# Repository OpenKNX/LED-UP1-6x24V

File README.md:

# LED-UP1-6x24V
OpenKNX 6channel LED PWM Controller up to 24V

see https://github.com/OpenKNX/OpenKNX/wiki/LED-UP1-6x24V

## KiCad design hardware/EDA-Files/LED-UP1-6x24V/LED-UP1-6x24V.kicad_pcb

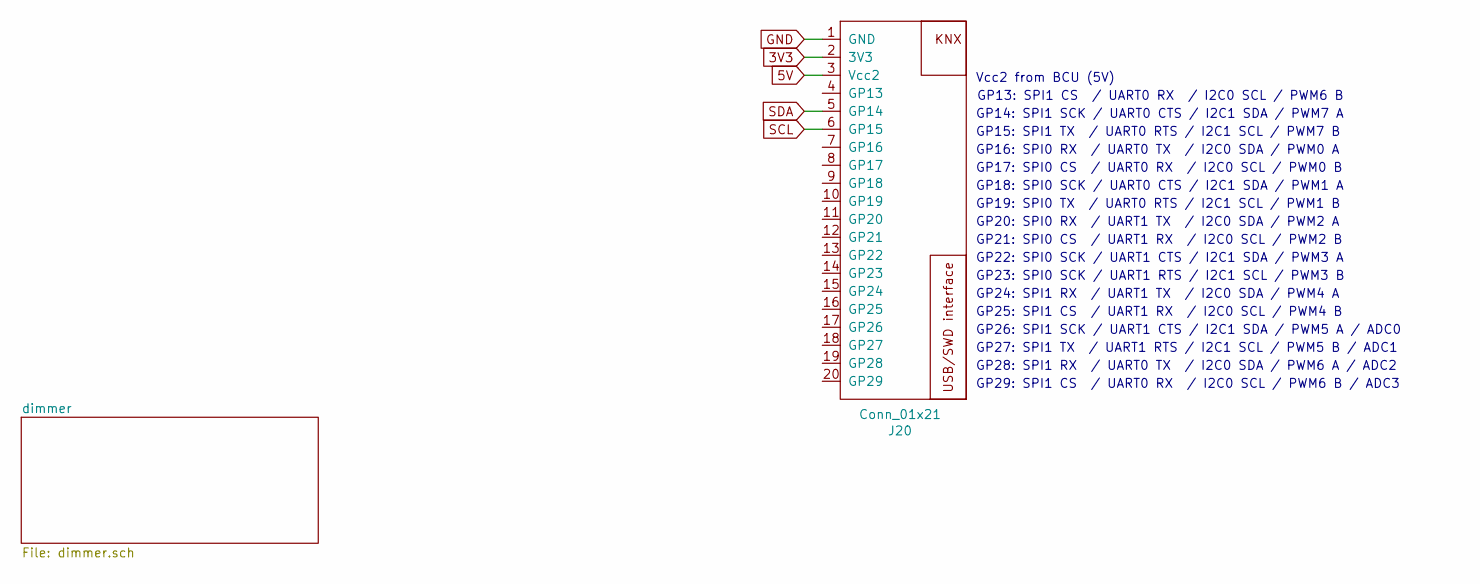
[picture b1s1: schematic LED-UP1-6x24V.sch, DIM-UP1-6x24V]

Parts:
J20: Conn_01x21; OpenKNX_UP1-PCBConnector_1x20_App_3D

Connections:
3V3: J20.2 (3V3); also elsewhere on the board
5V: J20.3 (Vcc2)
GND: J20.1 (GND); also elsewhere on the board
SCL: J20.6 (GP15); also elsewhere on the board
SDA: J20.5 (GP14); also elsewhere on the board

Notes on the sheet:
GP14: SPI1 SCK / UART0 CTS / I2C1 SDA / PWM7 A
GP15: SPI1 TX / UART0 RTS / I2C1 SCL / PWM7 B
GP18: SPI0 SCK / UART0 CTS / I2C1 SDA / PWM1 A
GP19: SPI0 TX / UART0 RTS / I2C1 SCL / PWM1 B
GP17: SPI0 CS / UART0 RX / I2C0 SCL / PWM0 B
GP16: SPI0 RX / UART0 TX / I2C0 SDA / PWM0 A
GP13: SPI1 CS / UART0 RX / I2C0 SCL / PWM6 B
GP20: SPI0 RX / UART1 TX / I2C0 SDA / PWM2 A
GP21: SPI0 CS / UART1 RX / I2C0 SCL / PWM2 B
GP22: SPI0 SCK / UART1 CTS / I2C1 SDA / PWM3 A
GP23: SPI0 SCK / UART1 RTS / I2C1 SCL / PWM3 B
GP24: SPI1 RX / UART1 TX / I2C0 SDA / PWM4 A
GP25: SPI1 CS / UART1 RX / I2C0 SCL / PWM4 B
GP26: SPI1 SCK / UART1 CTS / I2C1 SDA / PWM5 A / ADC0
GP27: SPI1 TX / UART1 RTS / I2C1 SCL / PWM5 B / ADC1
GP28: SPI1 RX / UART0 TX / I2C0 SDA / PWM6 A / ADC2
GP29: SPI1 CS / UART0 RX / I2C0 SCL / PWM6 B / ADC3
Vcc2 from BCU (5V)

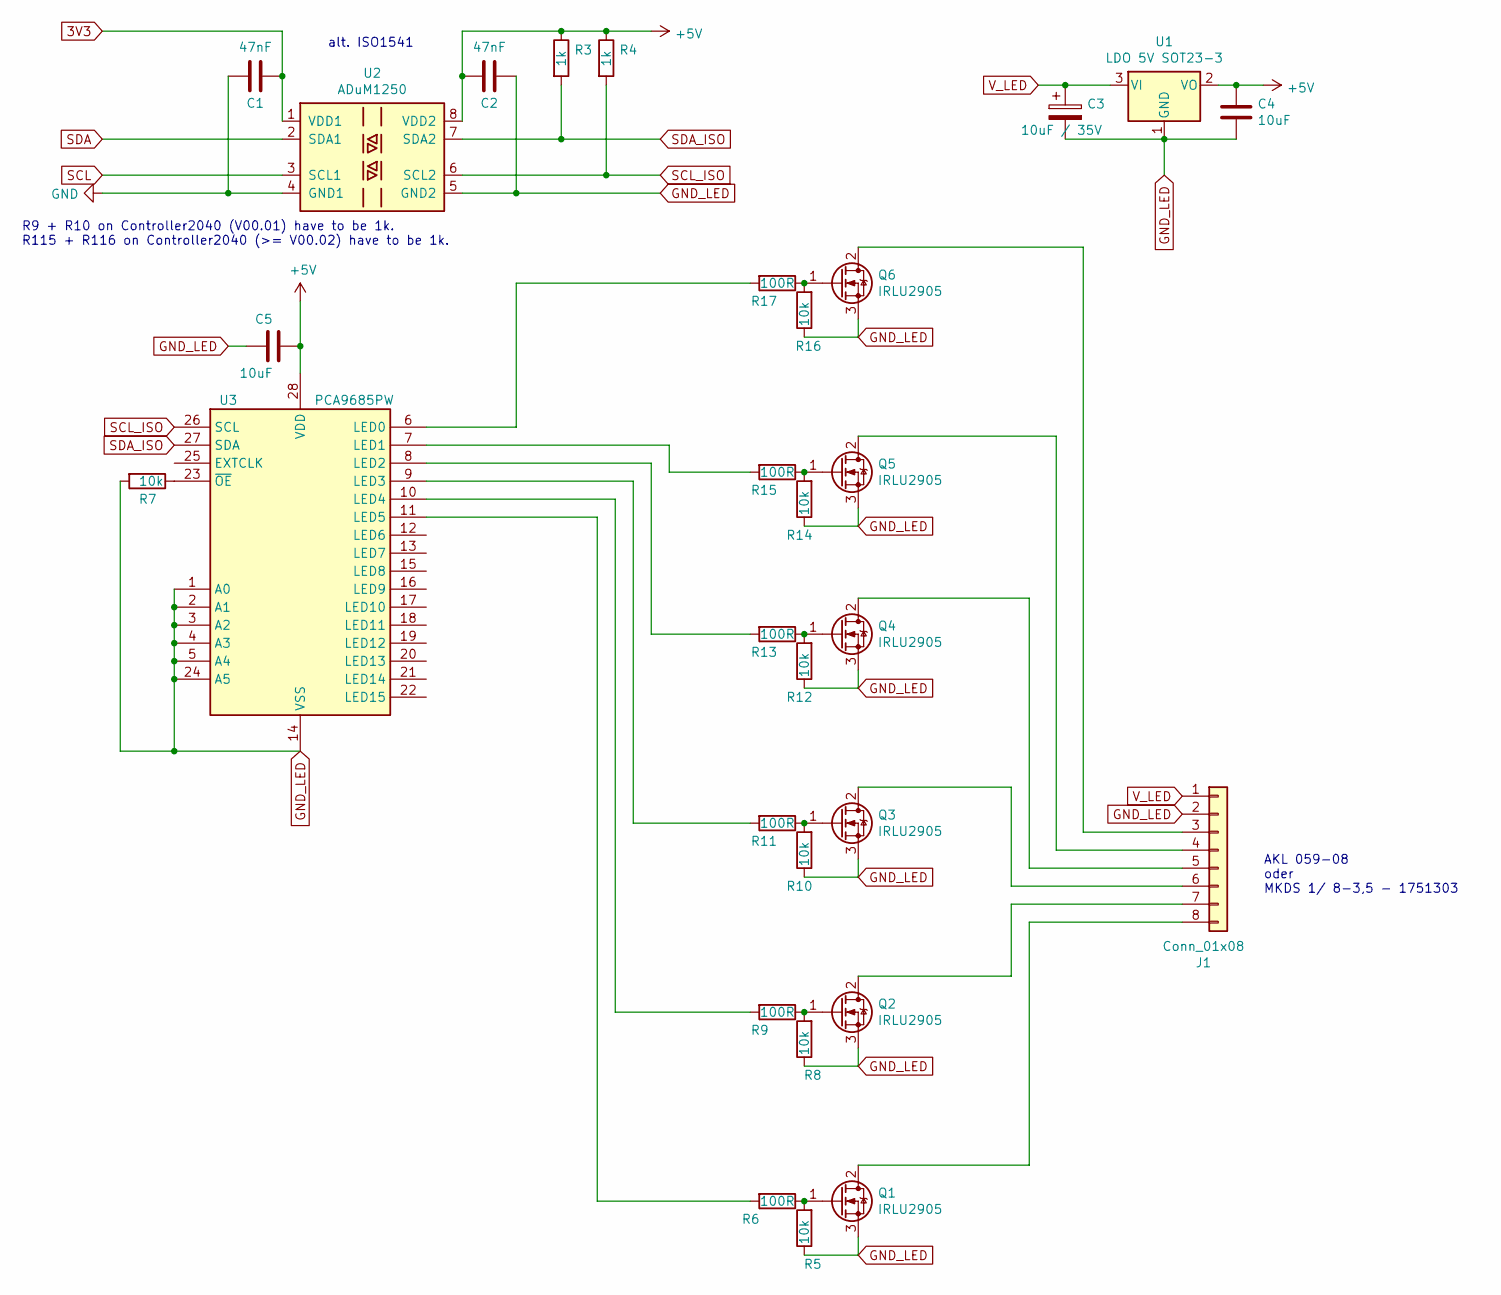
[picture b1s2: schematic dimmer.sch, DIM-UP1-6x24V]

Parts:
C1, C2: 47nF; C_0805_2012Metric_Pad1.15x1.40mm_HandSolder
C3: 10uF / 35V; CP_Elec_5x5.3
C4: 10uF; C_0603_1608Metric_Pad1.05x0.95mm_HandSolder
C5: 10uF; C_0805_2012Metric
J1: Conn_01x08; PhoenixContact_MKDS_1,5_8-G-3.5_1x08_P3.5mm_Horizontal
Q1, Q2, Q3, Q4, Q5, Q6: IRLU2905; TO-251-3_Vertical_lowprofile
R3, R4: 1k; R_0603_1608Metric_Pad1.05x0.95mm_HandSolder
R5, R7, R8, R10, R12, R14, R16: 10k; R_0603_1608Metric_Pad1.05x0.95mm_HandSolder
R6, R9, R11, R13, R15, R17: 100R; R_0603_1608Metric_Pad1.05x0.95mm_HandSolder
U1: LDO 5V SOT23-3; TSOT-23
U2: ADuM1250; SSOP-8_3.9x5.05mm_P1.27mm
U3: PCA9685PW; TSSOP-28_4.4x9.7mm_P0.65mm_Handsolder

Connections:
3V3: C1.1, U2.1 (VDD1); also elsewhere on the board
+5V: C2.2, C4.1, C5.2, R3.1, R4.1, U1.2 (VO), U2.8 (VDD2), U3.28 (VDD)
GND: C1.2, U2.4 (GND1); also elsewhere on the board
GND_LED: C2.1, C3.2, C4.2, C5.1, J1.2, Q1.3 (S), Q2.3 (S), Q3.3 (S), Q4.3 (S), Q5.3 (S), Q6.3 (S), R5.1, R7.2, R8.1, R10.1, R12.1, R14.1, R16.1, U1.1 (GND), U2.5 (GND2), U3.1 (A0), U3.2 (A1), U3.3 (A2), U3.4 (A3), U3.5 (A4), U3.14 (VSS), U3.24 (A5)
unnamed: J1.3, Q6.2 (D)
unnamed: J1.4, Q5.2 (D)
unnamed: J1.5, Q4.2 (D)
unnamed: J1.6, Q3.2 (D)
unnamed: J1.7, Q2.2 (D)
unnamed: J1.8, Q1.2 (D)
unnamed: Q1.1 (G), R5.2, R6.1
unnamed: Q2.1 (G), R8.2, R9.1
unnamed: Q3.1 (G), R10.2, R11.1
unnamed: Q4.1 (G), R12.2, R13.1
unnamed: Q5.1 (G), R14.2, R15.1
unnamed: Q6.1 (G), R16.2, R17.1
unnamed: R6.2, U3.11 (LED5)
unnamed: R7.1, U3.23 (~OE)
unnamed: R9.2, U3.10 (LED4)
unnamed: R11.2, U3.9 (LED3)
unnamed: R13.2, U3.8 (LED2)
unnamed: R15.2, U3.7 (LED1)
unnamed: R17.2, U3.6 (LED0)
SCL: U2.3 (SCL1); also elsewhere on the board
SCL_ISO: R4.2, U2.6 (SCL2), U3.26 (SCL)
SDA: U2.2 (SDA1); also elsewhere on the board
SDA_ISO: R3.2, U2.7 (SDA2), U3.27 (SDA)
V_LED: C3.1, J1.1, U1.3 (VI)

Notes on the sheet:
AKL 059-08 oder MKDS 1/ 8-3,5 - 1751303
R9 + R10 on Controller2040 (V00.01) have to be 1k. R115 + R116 on Controller2040 (>= V00.02) have to be 1k.
alt. ISO1541

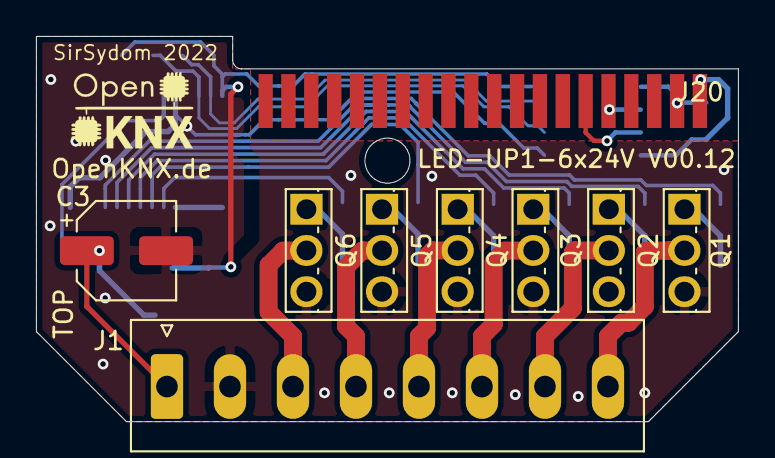
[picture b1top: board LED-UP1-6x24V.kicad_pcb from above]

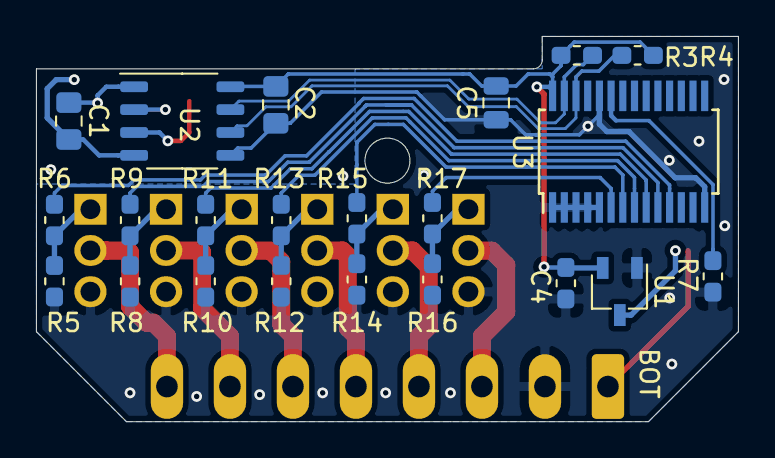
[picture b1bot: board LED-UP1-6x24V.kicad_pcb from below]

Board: 2 copper layers, 39.0 x 21.4 mm, 31 parts (22 on the bottom side), 28 nets.

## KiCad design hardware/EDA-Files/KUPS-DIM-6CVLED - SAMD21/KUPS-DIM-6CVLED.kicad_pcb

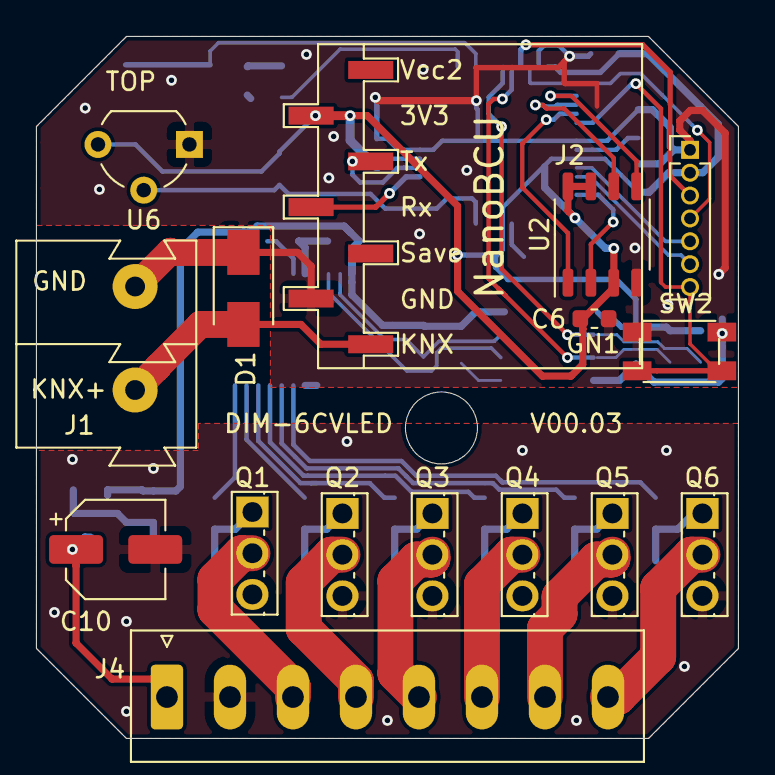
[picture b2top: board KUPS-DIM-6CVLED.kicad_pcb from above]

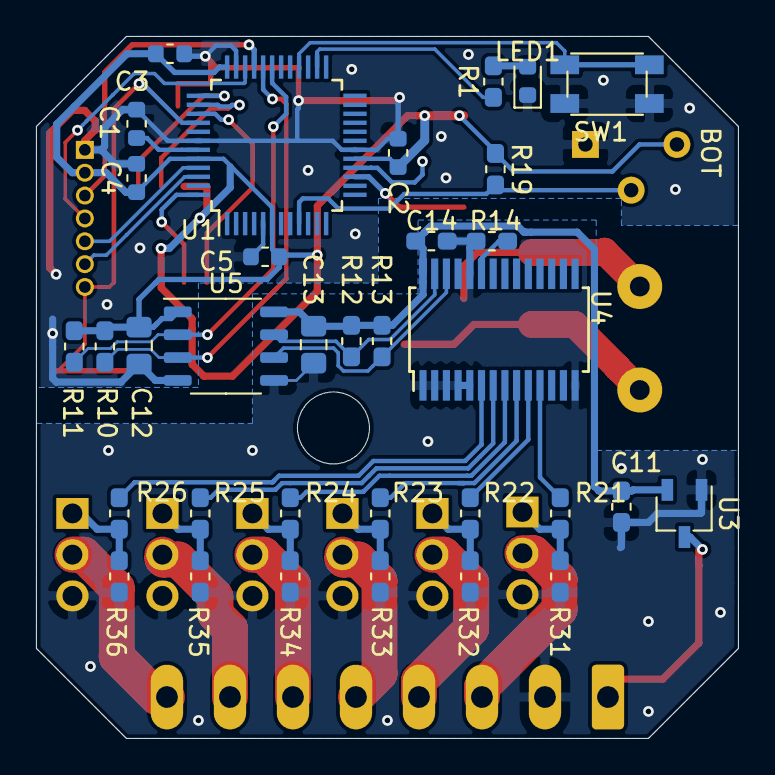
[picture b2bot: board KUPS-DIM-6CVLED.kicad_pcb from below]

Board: 2 copper layers, 39.0 x 39.0 mm, 50 parts (34 on the bottom side), 45 nets.

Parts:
C1, C2, C3, C4, C5, C6: 1µF; C_0603_1608Metric
C10: 10uF / 35V; CP_Elec_5x5.3
C11, C14: 10uF; C_0603_1608Metric_Pad1.05x0.95mm_HandSolder
C12, C13: 47nF; C_0805_2012Metric_Pad1.15x1.40mm_HandSolder
D1: SMAJ40CA; D_SMA
GN1: Konnekting_µBCU; NanoBCU_PinHeader_SMD_low_profile
J1: KNX_Conn; KNX_Connector
J2: SWD_USB; PinHeader_1x07_P1.27mm_Vertical
J4: Conn_01x08; PhoenixContact_MKDS_1,5_8-G-3.5_1x08_P3.5mm_Horizontal
LED1: LED; LED_0603_1608Metric
Q1, Q2, Q3, Q4, Q5, Q6: IRLU2905; TO-251-3_Vertical_lowprofile
R1, R10, R11, R12, R13: 1k; R_0603_1608Metric_Pad1.05x0.95mm_HandSolder
R14, R31, R32, R33, R34, R35, R36: 10k; R_0603_1608Metric_Pad1.05x0.95mm_HandSolder
R19: 4k7; R_0603_1608Metric_Pad1.05x0.95mm_HandSolder
R21, R22, R23, R24, R25, R26: 100R; R_0603_1608Metric_Pad1.05x0.95mm_HandSolder
SW1: Prog; SW_Push_Xunpu_TS-1089S_Handsolder
SW2: Reset; SW_Push_Xunpu_TS-1089S_Handsolder
U1: ATSAMD21G18; TQFP-48_7x7mm_P0.5mm
U2: GD25Q16C; SSOP-8_3.9x5.05mm_P1.27mm
U3: LDO 5V SOT23-3; TSOT-23
U4: PCA9685PW; TSSOP-28_4.4x9.7mm_P0.65mm_Handsolder
U5: ADuM1250; SSOP-8_3.9x5.05mm_P1.27mm
U6: DS18B20; TO-92_Wide

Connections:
+3V3: C2.1, C3.1, C4.1, C5.1, C6.1, C12.1, GN1.6, J2.2, R10.1, R11.1, R19.1, U1.6, U1.17, U1.36, U1.44, U2.3, U2.7, U2.8, U5.1, U6.3
+5V: C11.1, C13.2, C14.2, R12.1, R13.1, U3.2, U4.28, U5.8
A3: R19.2, U1.9, U6.2
D0: GN1.5, U1.16
D1: GN1.4, U1.15
D12: SW1.2, U1.28
D13: R1.1, U1.26
D+: J2.4, U1.34
D-: J2.3, U1.33
FLASH_CS: U1.39, U2.1
FLASH_MISO: U1.48, U2.2
FLASH_MOSI: U1.37, U2.5
FLASH_SCK: U1.38, U2.6
GND: C1.1, C2.2, C3.2, C4.2, C5.2, C6.2, C12.2, D1.1, GN1.2, J1.2, J2.1, LED1.1, SW1.1, SW2.1, U1.5, U1.18, U1.35, U1.42, U2.4, U5.4, U6.1
GND_LED: C10.2, C11.2, C13.1, C14.1, J4.2, Q1.3, Q2.3, Q3.3, Q4.3, Q5.3, Q6.3, R14.2, R31.1, R32.1, R33.1, R34.1, R35.1, R36.1, U3.1, U4.1, U4.2, U4.3, U4.4, U4.5, U4.14, U4.24, U5.5
KNX+: D1.2, GN1.1, J1.1
unnamed: C1.2, U1.43
unnamed: J4.3, Q1.2
unnamed: J4.4, Q2.2
unnamed: J4.5, Q3.2
unnamed: J4.6, Q4.2
unnamed: J4.7, Q5.2
unnamed: J4.8, Q6.2
unnamed: LED1.2, R1.2
unnamed: Q1.1, R21.1, R31.2
unnamed: Q2.1, R22.1, R32.2
unnamed: Q3.1, R23.1, R33.2
unnamed: Q4.1, R24.1, R34.2
unnamed: Q5.1, R25.1, R35.2
unnamed: Q6.1, R26.1, R36.2
unnamed: R14.1, U4.23
unnamed: R21.2, U4.11
unnamed: R22.2, U4.10
unnamed: R23.2, U4.9
unnamed: R24.2, U4.8
unnamed: R25.2, U4.7
unnamed: R26.2, U4.6
Reset: J2.7, SW2.2, U1.40
SCL: R10.2, U1.32, U5.3
SCL_ISO: R13.2, U4.26, U5.6
SDA: R11.2, U1.31, U5.2
SDA_ISO: R12.2, U4.27, U5.7
SWCLK: J2.5, U1.45
SWDIO: J2.6, U1.46
V_LED: C10.1, J4.1, U3.3

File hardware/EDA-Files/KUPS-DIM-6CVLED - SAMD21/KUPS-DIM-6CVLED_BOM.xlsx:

Id | Designator | Package | Quantity | Designation | Supplier and ref
1 | U4 | TSSOP-28_4.4x9.7mm_P0.65mm_Handsolder | 1 | PCA9685PW
2 | C14,C11 | C_0603_1608Metric_Pad1.05x0.95mm_HandSolder | 2 | 10uF
3 | R19 | R_0603_1608Metric_Pad1.05x0.95mm_HandSolder | 1 | 4k7
4 | C10 | CP_Elec_5x5.3 | 1 | 10uF / 35V
5 | U6 | TO-92_Inline | 1 | DS18B20
6 | R31,R32,R36,R35,R34,R33,R14 | R_0603_1608Metric_Pad1.05x0.95mm_HandSolder | 7 | 10k
7 | R21,R22,R26,R24,R23,R25 | R_0603_1608Metric_Pad1.05x0.95mm_HandSolder | 6 | 100R
8 | Q1,Q2,Q6,Q4,Q3,Q5 | TO-251-3_Vertical | 6 | IRLU2905
9 | J4 | PhoenixContact_MKDS_1,5_8-G-3.5_1x08_P3.5mm_Horizontal | 1 | Conn_01x08
10 | C13,C12 | C_0805_2012Metric_Pad1.15x1.40mm_HandSolder | 2 | 47nF
11 | GN1 | NanoBCU_PinHeader_SMD_low_profile | 1 | Konnekting_ÂµBCU
12 | U5 | SOIC-8_3.9x4.9mm_P1.27mm | 1 | ADuM1250
13 | U3 | TSOT-23 | 1 | LDO 5V SOT23-3
14 | R13,R12,R11,R10 | R_0603_1608Metric_Pad1.05x0.95mm_HandSolder | 4 | 1k
15 | R1 | R_0603_1608Metric_Pad1.05x0.95mm_HandSolder | 1 | R
16 | J1 | KNX_Connector | 1 | KNX_Conn
17 | SW2 | SW_Push_Xunpu_TS-1089S | 1 | Reset
18 | U2 | SOIC-8_3.9x4.9mm_P1.27mm | 1 | GD25Q16C
19 | C6,C5,C3,C2,C1,C4 | C_0603_1608Metric | 6 | 1ÂµF
20 | U1 | TQFP-48_7x7mm_P0.5mm | 1 | ATSAMD21G18
21 | J3 | PinHeader_1x04_P1.27mm_Vertical | 1 | USB
22 | J2 | PinHeader_1x04_P1.27mm_Vertical | 1 | SWD
23 | D1 | D_SMA | 1 | SMAJ40CA
24 | SW1 | SW_Push_Xunpu_TS-1089S | 1 | Prog
25 | LED1 | LED_0603_1608Metric | 1 | LED

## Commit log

2022-02-16 V00.11
2022-02-16 added docu
2022-02-24 first draft of case
2022-10-12 STL files for case 001
2023-12-05 moved data from gitlab repo
2024-03-29 New LED-UP1-4x24V
